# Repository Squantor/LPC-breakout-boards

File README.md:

# LPC microcontroller breakout boards
This is a small collection breakout boards for various LPC microcontrollers, in the future I might add others to the mix. Currently there are a set of eagle and kicad designs, the eagle designs are legacy and might get replaced in the future as currently I am fully comitting on using kicad.
## checkout notes
This repository contains a few submodules, so after checking out do not forget to also check out the submodules.
```
git clone https://github.com/Squantor/LPC-breakout-boards.git
git submodule init
git submodule update
```
Submodules are my private kicad library that are used in my projects. I do try to use the kicad components as much as possible but for certain component types they are less then optimal.

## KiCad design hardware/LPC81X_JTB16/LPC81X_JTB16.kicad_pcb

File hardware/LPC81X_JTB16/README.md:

# LPC812 XSON16 breakout
Breakout board for the LPC812 in XSON16 package. This is more or less a test bed to do everything as small as possible. So 0201 components, tiny crystal, everything tiny!
## TODO's
Still some things need to be done:
* schematic entry 
* PCB layout
* Review with one night in between
* Produce at [OSHPARK](https://oshpark.com/)
* Assemble
* Test & characterise
* update Readme.md with pictures and BOM
## BOM
* LPC812M101JTB16
* All passives are 0201

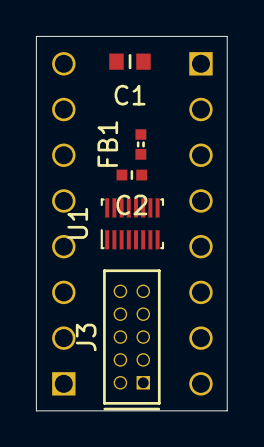
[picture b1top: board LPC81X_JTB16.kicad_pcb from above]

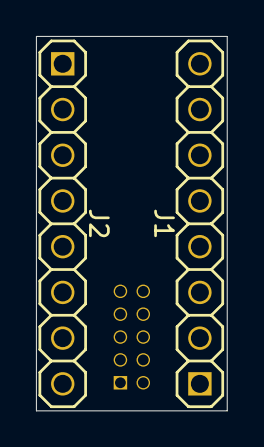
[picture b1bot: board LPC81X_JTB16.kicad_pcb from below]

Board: 2 copper layers, 10.6 x 20.8 mm, 9 parts (2 on the bottom side), 11 nets, no tracks yet.

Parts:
C1: 10u; C_0603
C2: 1u; C_0402
FB1: 600; L_0402
J1, J2: Conn_01x08; Header-0254-1X08-H010
J3: JTAG_2X05_IN; Header-0127-2X05-H006
N1: 20200720; Label_Generic
N2: OHWLOGO; OSHW-Symbol_6.7x6mm_SilkScreen
U1: LPC812M101JTB16; NXP_XSON-16

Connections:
/PIO0_2: J2.7, U1.6
/PIO0_3: J2.8, U1.5
/PIO0_4: J1.1, U1.4
/PIO0_5: J1.2, U1.3
/PIO0_10: J2.5, U1.8
/PIO0_11: J2.6, U1.7
/PIO0_12: J1.3, U1.2
/PIO0_13: J1.4, U1.1
/VDD: C1.1, FB1.2, J3.1
/VSS: C1.2, C2.2, J3.3, J3.5, J3.9, U1.13
unnamed: C2.1, FB1.1, U1.12

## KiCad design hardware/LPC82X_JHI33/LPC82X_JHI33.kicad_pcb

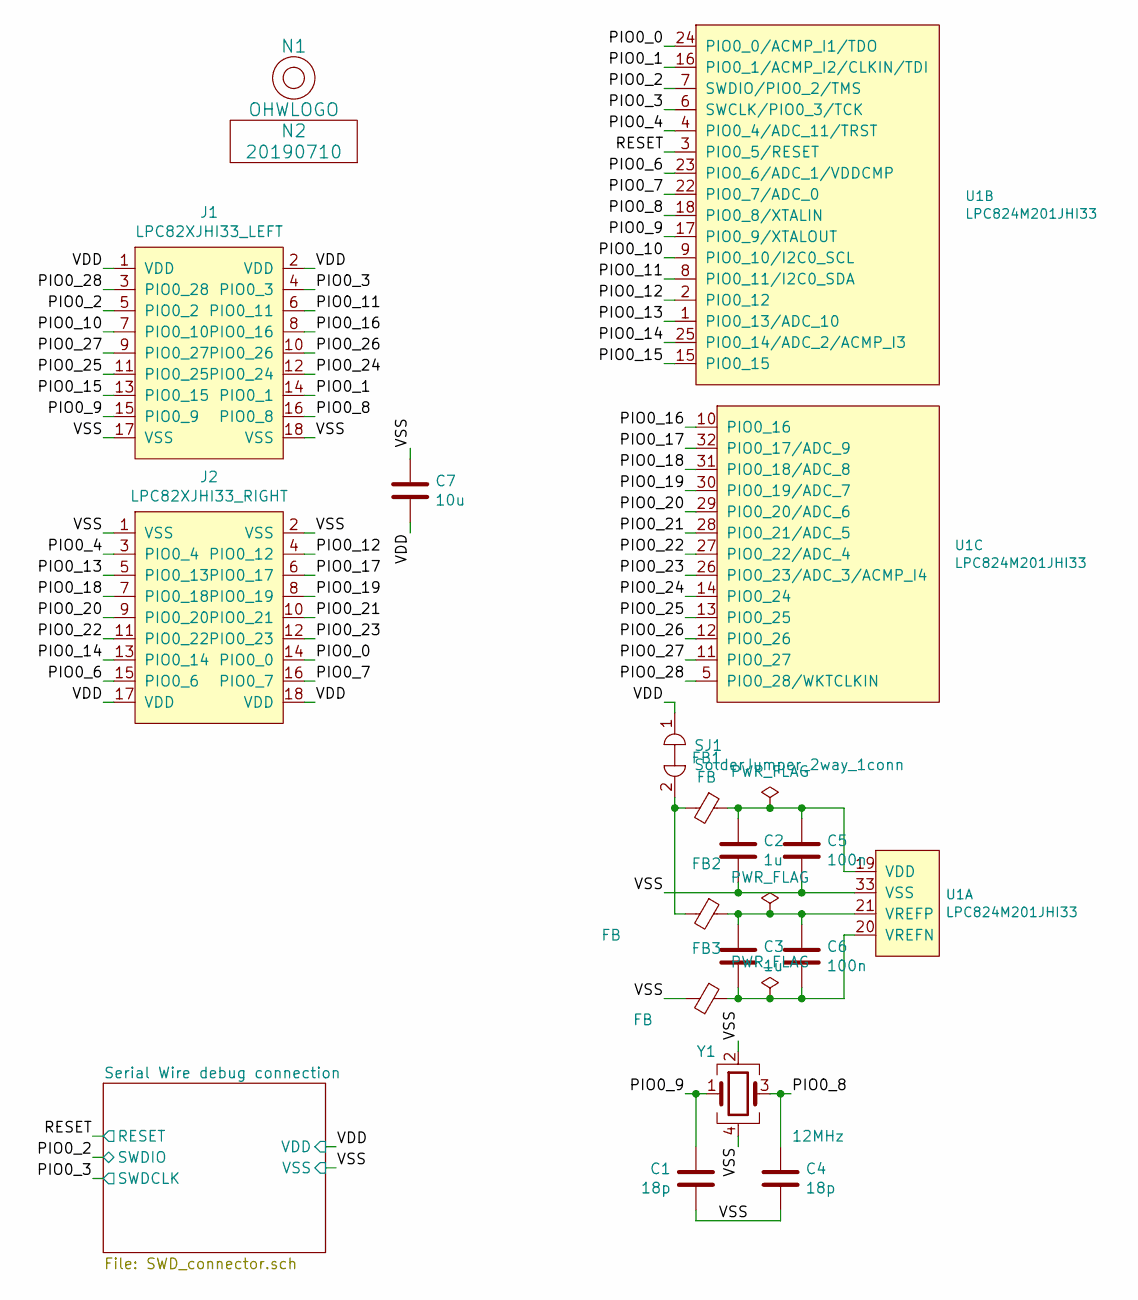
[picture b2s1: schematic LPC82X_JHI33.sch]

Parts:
C1, C4: 18p; C_0402
C2, C3: 1u; C_0603
C5, C6: 100n; C_0402
C7: 10u; C_0805
FB1, FB2, FB3: FB; C_0402
J1: LPC82XJHI33_LEFT; LPC82XJHI33_breakout_left
J2: LPC82XJHI33_RIGHT; LPC82XJHI33_breakout_right
N1: OHWLOGO; OSHW-Symbol_6.7x6mm_SilkScreen
N2: 20190710; Label_version
SJ1: SolderJumper_2way_1conn; solder_jumper_2way_conn
U1: LPC824M201JHI33; SOT617-3_alt_paste
Y1: 12MHz; Crystal_3225_4

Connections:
/PIO0_0: J2.14 (PIO0_0), U1.24 (PIO0_0/ACMP_I1/TDO)
/PIO0_1: J1.14 (PIO0_1), U1.16 (PIO0_1/ACMP_I2/CLKIN/TDI)
/PIO0_2: J1.5 (PIO0_2), U1.7 (SWDIO/PIO0_2/TMS); also elsewhere on the board
/PIO0_3: J1.4 (PIO0_3), U1.6 (SWCLK/PIO0_3/TCK); also elsewhere on the board
/PIO0_4: J2.3 (PIO0_4), U1.4 (PIO0_4/ADC_11/TRST)
/PIO0_6: J2.15 (PIO0_6), U1.23 (PIO0_6/ADC_1/VDDCMP)
/PIO0_7: J2.16 (PIO0_7), U1.22 (PIO0_7/ADC_0)
/PIO0_8: C4.1, J1.16 (PIO0_8), U1.18 (PIO0_8/XTALIN), Y1.3
/PIO0_9: C1.1, J1.15 (PIO0_9), U1.17 (PIO0_9/XTALOUT), Y1.1
/PIO0_10: J1.7 (PIO0_10), U1.9 (PIO0_10/I2C0_SCL)
/PIO0_11: J1.6 (PIO0_11), U1.8 (PIO0_11/I2C0_SDA)
/PIO0_12: J2.4 (PIO0_12), U1.2 (PIO0_12)
/PIO0_13: J2.5 (PIO0_13), U1.1 (PIO0_13/ADC_10)
/PIO0_14: J2.13 (PIO0_14), U1.25 (PIO0_14/ADC_2/ACMP_I3)
/PIO0_15: J1.13 (PIO0_15), U1.15 (PIO0_15)
/PIO0_16: J1.8 (PIO0_16), U1.10 (PIO0_16)
/PIO0_17: J2.6 (PIO0_17), U1.32 (PIO0_17/ADC_9)
/PIO0_18: J2.7 (PIO0_18), U1.31 (PIO0_18/ADC_8)
/PIO0_19: J2.8 (PIO0_19), U1.30 (PIO0_19/ADC_7)
/PIO0_20: J2.9 (PIO0_20), U1.29 (PIO0_20/ADC_6)
/PIO0_21: J2.10 (PIO0_21), U1.28 (PIO0_21/ADC_5)
/PIO0_22: J2.11 (PIO0_22), U1.27 (PIO0_22/ADC_4)
/PIO0_23: J2.12 (PIO0_23), U1.26 (PIO0_23/ADC_3/ACMP_I4)
/PIO0_24: J1.12 (PIO0_24), U1.14 (PIO0_24)
/PIO0_25: J1.11 (PIO0_25), U1.13 (PIO0_25)
/PIO0_26: J1.10 (PIO0_26), U1.12 (PIO0_26)
/PIO0_27: J1.9 (PIO0_27), U1.11 (PIO0_27)
/PIO0_28: J1.3 (PIO0_28), U1.5 (PIO0_28/WKTCLKIN)
/RESET: U1.3 (PIO0_5/RESET); also elsewhere on the board
/VDD: C7.2, J1.1 (VDD), J1.2 (VDD), J2.17 (VDD), J2.18 (VDD), SJ1.1; also elsewhere on the board
/VSS: C1.2, C2.2, C4.2, C5.2, C7.1, FB3.2, J1.17 (VSS), J1.18 (VSS), J2.1 (VSS), J2.2 (VSS), U1.33 (VSS), Y1.2, Y1.4; also elsewhere on the board
unnamed: C2.1, C5.1, FB1.1, U1.19 (VDD)
unnamed: C3.1, C6.1, FB2.1, U1.21 (VREFP)
unnamed: C3.2, C6.2, FB3.1, U1.20 (VREFN)
unnamed: FB1.2, FB2.2, SJ1.2

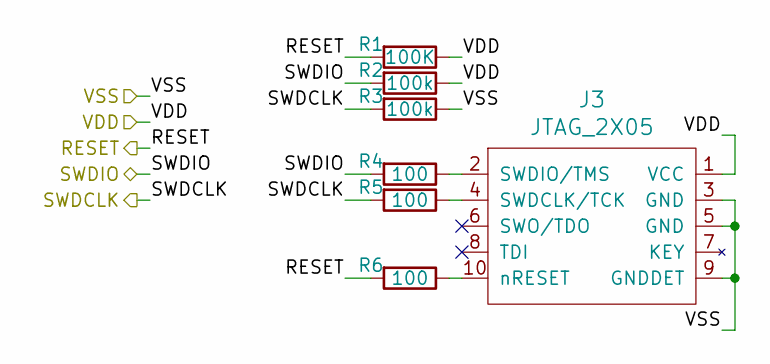
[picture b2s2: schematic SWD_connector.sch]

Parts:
J3: JTAG_2X05; Header-0127-2X05-H006
R1: 100K; R_0402_hand
R2, R3: 100k; R_0402_hand
R4, R5, R6: 100; R_0402_hand

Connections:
/PIO0_2: R2.2, R4.2; also elsewhere on the board
/PIO0_3: R3.2, R5.2; also elsewhere on the board
/RESET: R1.2, R6.2; also elsewhere on the board
/VDD: J3.1 (VCC), R1.1, R2.1; also elsewhere on the board
/VSS: J3.3 (GND), J3.5 (GND), J3.9 (GNDDET), R3.1; also elsewhere on the board
unnamed: J3.2 (SWDIO/TMS), R4.1
unnamed: J3.4 (SWDCLK/TCK), R5.1
unnamed: J3.10 (nRESET), R6.1

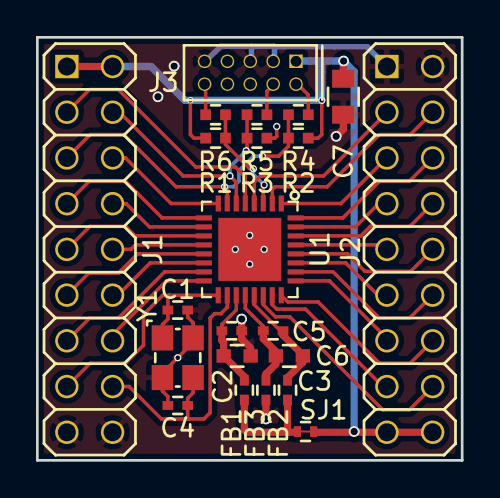
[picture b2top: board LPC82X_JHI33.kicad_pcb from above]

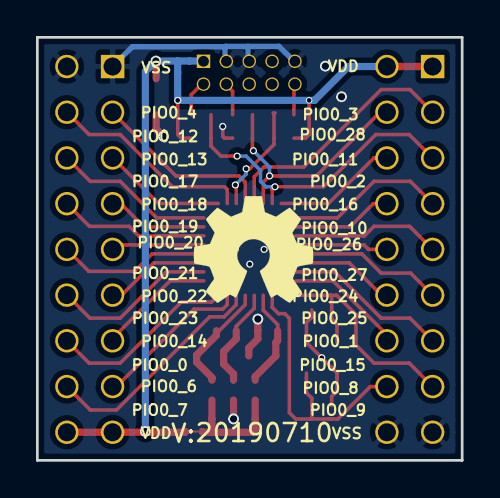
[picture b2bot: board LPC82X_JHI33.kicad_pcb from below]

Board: 2 copper layers, 23.6 x 23.5 mm, 24 parts (2 on the bottom side), 38 nets.

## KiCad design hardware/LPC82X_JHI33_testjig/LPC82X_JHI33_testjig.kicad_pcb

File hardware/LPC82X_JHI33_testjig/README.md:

# LPC824JHI33 test jig PCB
This PCB is used in the LPC824JHI33 test jig. It contains a network of resistors and capacitors that is used by the test algorithm. See in the software directory the breakout tester how this works in detail.
## TODO's
Still some things need to be done:
* schematic entry (TODO)
* PCB layout (TODO)
* Review with one night in between (TODO)
* Produce at [OSHPARK](https://oshpark.com/) (TODO)
* Assemble (TODO)
* Test & characterise (TODO)
* update Readme.md with pictures and BOM (TODO)

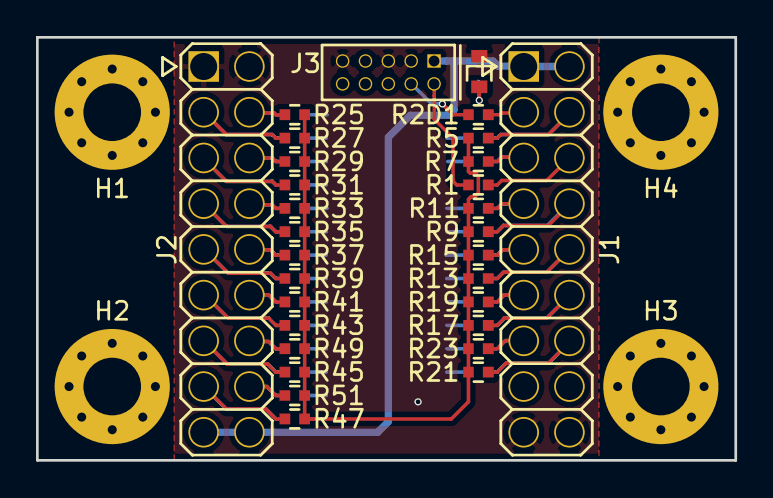
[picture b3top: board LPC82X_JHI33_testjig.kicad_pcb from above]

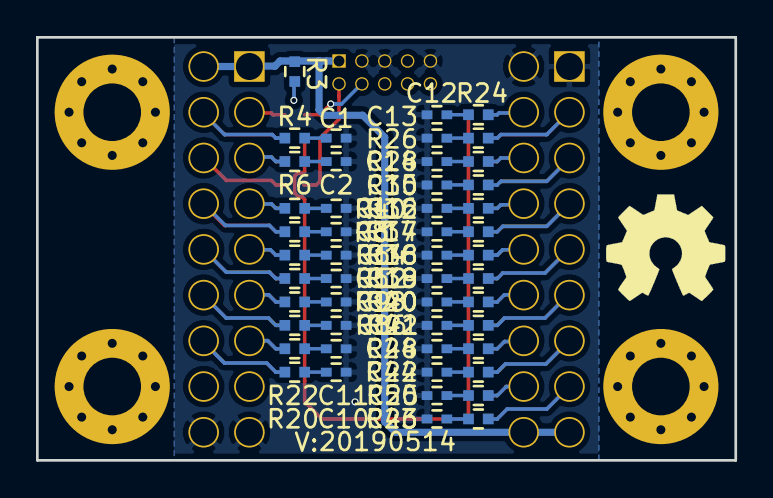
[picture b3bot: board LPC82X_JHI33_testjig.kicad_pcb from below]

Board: 2 copper layers, 38.8 x 23.5 mm, 85 parts (51 on the bottom side), 56 nets.

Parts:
C1, C2, C3, C4, C5, C6, C8, C9, C10, C11, C12, C13, C14, C15, C16, C17, C18, C19, C20, C21, C22, C23, C24, C25: 1u; C_0402
D1: RED; D_0603_hand
H1, H2, H3, H4: MountingHole; MountingHole_3.2mm_M3_Pad_Via
J1: LPC82XJHI33_LEFT; Header-0254-2X09-H015
J2: LPC82XJHI33_RIGHT; Header-0254-2X09-H015
J3: JTAG_2X05; Header-0127-2X05-H006
N1: OHWLOGO; OSHW-Symbol_6.7x6mm_SilkScreen
N2: 20190514; Label_version
R1, R2: 100; R_0402_hand
R3: 1K; R_0402_hand
R4, R6, R8, R10, R12, R14, R16, R18, R20, R22, R24, R26, R28, R30, R32, R34, R36, R38, R40, R42, R44, R46, R48, R50: 470; R_0402_hand
R5, R7, R9, R11, R13, R15, R17, R19, R21, R23, R25, R27, R29, R31, R33, R35, R37, R39, R41, R43, R45, R47, R49, R51: 100K; R_0402_hand

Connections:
/Digital_stimulus: R5.1, R7.1, R9.1, R11.1, R13.1, R15.1, R17.1, R19.1, R21.1, R23.1, R25.1, R27.1, R29.1, R31.1, R33.1, R35.1, R37.1, R39.1, R41.1, R43.1, R45.1, R47.1, R49.1, R51.1
/PIO0_0: J2.13, R44.2, R45.2
/PIO0_1: J1.13, R22.2, R23.2
/PIO0_2: J1.6, R1.2
/PIO0_3: J1.3, R2.2
/PIO0_4: J2.4, R24.2, R25.2
/PIO0_6: J2.16, R50.2, R51.2
/PIO0_7: J2.15, R46.2, R47.2
/PIO0_10: J1.8, R8.2, R9.2
/PIO0_11: J1.5, R6.2, R7.2
/PIO0_12: J2.3, R26.2, R27.2
/PIO0_13: J2.6, R28.2, R29.2
/PIO0_14: J2.14, R48.2, R49.2
/PIO0_15: J1.14, R20.2, R21.2
/PIO0_16: J1.7, R10.2, R11.2
/PIO0_17: J2.5, R30.2, R31.2
/PIO0_18: J2.8, R32.2, R33.2
/PIO0_19: J2.7, R34.2, R35.2
/PIO0_20: J2.10, R36.2, R37.2
/PIO0_21: J2.9, R38.2, R39.2
/PIO0_22: J2.12, R40.2, R41.2
/PIO0_23: J2.11, R42.2, R43.2
/PIO0_24: J1.11, R18.2, R19.2
/PIO0_25: J1.12, R16.2, R17.2
/PIO0_26: J1.9, R14.2, R15.2
/PIO0_27: J1.10, R12.2, R13.2
/PIO0_28: J1.4, R4.2, R5.2
/VDD: J1.1, J1.2, J2.17, J2.18, J3.1, R3.1
/VSS: C1.2, C2.2, C3.2, C4.2, C5.2, C6.2, C8.2, C9.2, C10.2, C11.2, C12.2, C13.2, C14.2, C15.2, C16.2, C17.2, C18.2, C19.2, C20.2, C21.2, C22.2, C23.2, C24.2, C25.2, D1.1, J1.17, J1.18, J2.1, J2.2, J3.3, J3.5, J3.9
unnamed: C1.1, R4.1
unnamed: C2.1, R6.1
unnamed: C3.1, R8.1
unnamed: C4.1, R10.1
unnamed: C5.1, R12.1
unnamed: C6.1, R14.1
unnamed: C8.1, R16.1
unnamed: C9.1, R18.1
unnamed: C10.1, R20.1
unnamed: C11.1, R22.1
unnamed: C12.1, R24.1
unnamed: C13.1, R26.1
unnamed: C14.1, R28.1
unnamed: C15.1, R30.1
unnamed: C16.1, R32.1
unnamed: C17.1, R34.1
unnamed: C18.1, R36.1
unnamed: C19.1, R38.1
unnamed: C20.1, R40.1
unnamed: C21.1, R42.1
unnamed: C22.1, R44.1
unnamed: C23.1, R46.1
unnamed: C24.1, R48.1
unnamed: C25.1, R50.1
unnamed: D1.2, R3.2
unnamed: J3.2, R1.1
unnamed: J3.4, R2.1

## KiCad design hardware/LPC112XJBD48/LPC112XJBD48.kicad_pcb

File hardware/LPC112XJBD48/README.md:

# LPC112X QFP48 breakout board
Breakout board of [LPC112X](https://www.nxp.com/products/processors-and-microcontrollers/arm-based-processors-and-mcus/lpc-cortex-m-mcus/lpc1100-cortex-m0-plus-m0/scalable-entry-level-32-bit-microcontroller-mcu-based-on-arm-cortex-m0-cores:LPC1100)
## TODO's
Still some things need to be done:
* schematic entry (TODO)
* PCB layout (TODO)
* Review with one night in between (TODO)
* Produce at [OSHPARK](https://oshpark.com/) (TODO)
* Assemble (TODO)
* Test & characterise (TODO)
* update Readme.md with pictures and BOM (TODO)

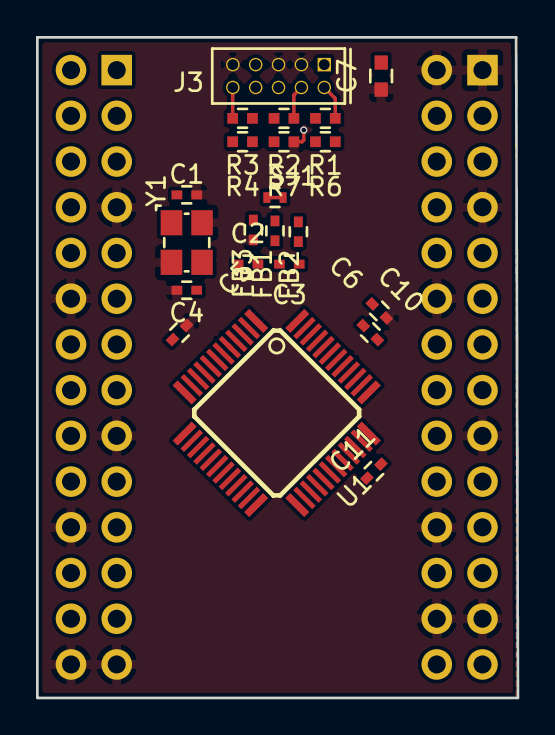
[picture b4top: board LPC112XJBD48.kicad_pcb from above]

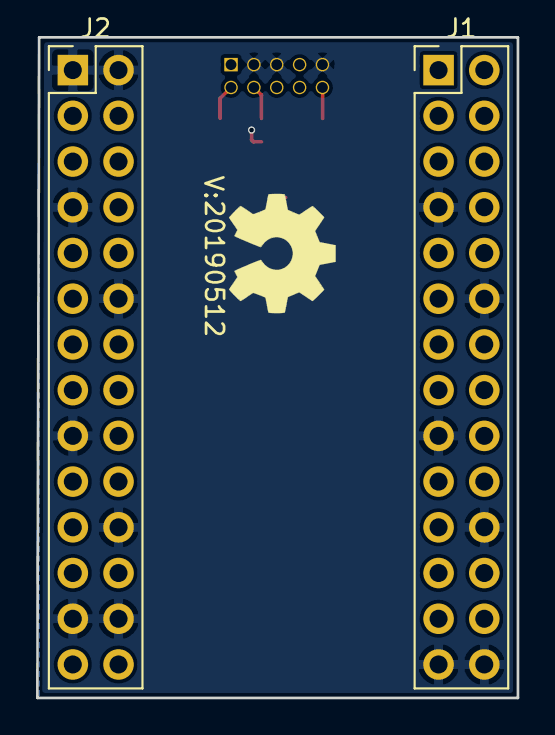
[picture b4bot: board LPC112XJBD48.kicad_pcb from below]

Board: 2 copper layers, 26.7 x 36.7 mm, 26 parts (4 on the bottom side), 49 nets.

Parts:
C1, C4: 18p; C_0402
C2, C3: 1u; C_0402
C5, C6, C10, C11: 100n; C_0402
C7: 10u; C_0603
FB1, FB2, FB3: 600; C_0402
J1, J2: Conn_02x14_Odd_Even; PinHeader_2x14_P2.54mm_Vertical
J3: JTAG_2X05; Header-0127-2X05-H006
N1: OHWLOGO; OSHW-Symbol_6.7x6mm_SilkScreen
N2: 20190512; Label_version
R1, R2, R3: 100; R_0402_hand
R4: 100K; R_0402_hand
R6, R7: 100k; R_0402_hand
SJ1: SolderJumper_2way_1conn; solder_jumper_2way_conn
U1: LPC1125JBD48_303; SOT313-2-NXP
Y1: 12MHz; Crystal_3225_4

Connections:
/PIO0_1: J1.6, U1.4
/PIO0_2: J1.9, U1.10
/PIO0_3: J1.14, U1.14
/PIO0_4: J1.15, U1.15
/PIO0_5: J1.16, U1.16
/PIO0_6: J1.24, U1.22
/PIO0_7: J1.25, U1.23
/PIO0_8: J2.23, U1.26
/PIO0_9: J2.21, U1.27
/PIO0_10: J2.20, R2.2, R7.2, U1.28
/PIO0_11: J2.18, U1.30
/PIO1_0: J2.16, U1.31
/PIO1_1: J2.15, U1.32
/PIO1_2: J2.14, U1.35
/PIO1_3: J2.10, R1.2, R6.2, U1.38
/PIO1_4: J2.9, U1.39
/PIO1_5: J2.6, U1.45
/PIO1_6: J2.5, U1.46
/PIO1_7: J2.4, U1.47
/PIO1_8: J1.8, U1.9
/PIO1_9: J1.18, U1.17
/PIO1_10: J2.19, U1.29
/PIO1_11: J2.8, U1.42
/PIO2_0: J1.4, U1.2
/PIO2_1: J1.13, U1.13
/PIO2_2: J2.24, U1.25
/PIO2_3: J2.11, U1.37
/PIO2_4: J1.20, U1.19
/PIO2_5: J1.21, U1.20
/PIO2_6: J1.3, U1.1
/PIO2_7: J1.10, U1.11
/PIO2_8: J1.11, U1.12
/PIO2_9: J1.26, U1.24
/PIO3_0: J2.13, U1.36
/PIO3_3: J2.3, U1.48
/PIO3_4: J1.19, U1.18
/PIO3_5: J1.23, U1.21
/RESET: J1.5, R3.2, R4.2, U1.3
/XTALIN: C4.1, U1.6, Y1.3
/XTALOUT: C1.1, U1.7, Y1.1
unnamed: C2.1, C5.1, C10.1, FB1.1, U1.8, U1.44
unnamed: C3.1, C6.1, C11.1, FB2.1, U1.33, U1.43
unnamed: C3.2, C6.2, C11.2, FB3.1, U1.34, U1.40
unnamed: FB1.2, FB2.2, SJ1.1
unnamed: J3.2, R1.1
unnamed: J3.4, R2.1
unnamed: J3.10, R3.1
VDD: C7.2, J1.1, J1.2, J2.27, J2.28, J3.1, R4.1, R6.1, SJ1.2
VSS: C1.2, C2.2, C4.2, C5.2, C7.1, C10.2, FB3.2, J1.7, J1.12, J1.17, J1.22, J1.27, J1.28, J2.1, J2.2, J2.7, J2.12, J2.17, J2.22, J2.25, J2.26, J3.3, J3.5, J3.9, R7.1, U1.5, U1.41, Y1.2, Y1.4

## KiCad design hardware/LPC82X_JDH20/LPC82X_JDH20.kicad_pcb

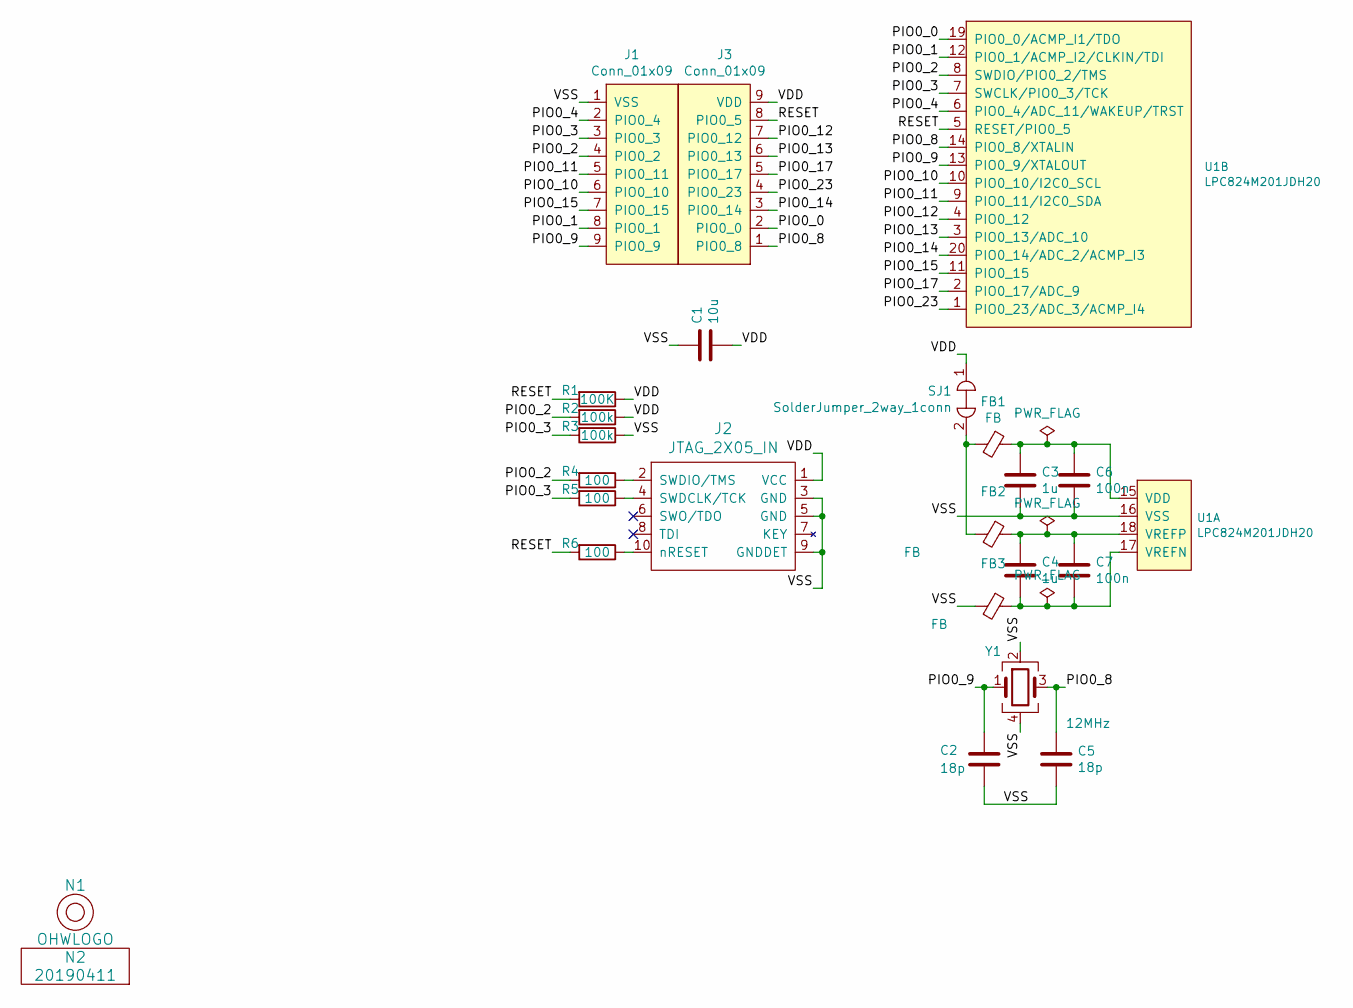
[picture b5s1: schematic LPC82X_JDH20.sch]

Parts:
C1: 10u; C_0805
C2, C5: 18p; C_0402
C3, C4: 1u; C_0603
C6, C7: 100n; C_0402
FB1, FB2, FB3: FB; C_0402
J1: Conn_01x09; LPC82XJDH20_breakout_left
J2: JTAG_2X05_IN; Header-0127-2X05-H006
J3: Conn_01x09; LPC82XJDH20_breakout_right
N1: OHWLOGO; OSHW-Symbol_6.7x6mm_SilkScreen
N2: 20190411; Label_version
R1: 100K; R_0402_hand
R2, R3: 100k; R_0402_hand
R4, R5, R6: 100; R_0402_hand
SJ1: SolderJumper_2way_1conn; solder_jumper_2way_conn
U1: LPC824M201JDH20; SOT360
Y1: 12MHz; Crystal_3225_4

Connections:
/PIO0_0: J3.2 (PIO0_0), U1.19 (PIO0_0/ACMP_I1/TDO)
/PIO0_1: J1.8 (PIO0_1), U1.12 (PIO0_1/ACMP_I2/CLKIN/TDI)
/PIO0_2: J1.4 (PIO0_2), R2.2, R4.2, U1.8 (SWDIO/PIO0_2/TMS)
/PIO0_3: J1.3 (PIO0_3), R3.2, R5.2, U1.7 (SWCLK/PIO0_3/TCK)
/PIO0_4: J1.2 (PIO0_4), U1.6 (PIO0_4/ADC_11/WAKEUP/TRST)
/PIO0_8: C5.1, J3.1 (PIO0_8), U1.14 (PIO0_8/XTALIN), Y1.3
/PIO0_9: C2.1, J1.9 (PIO0_9), U1.13 (PIO0_9/XTALOUT), Y1.1
/PIO0_10: J1.6 (PIO0_10), U1.10 (PIO0_10/I2C0_SCL)
/PIO0_11: J1.5 (PIO0_11), U1.9 (PIO0_11/I2C0_SDA)
/PIO0_12: J3.7 (PIO0_12), U1.4 (PIO0_12)
/PIO0_13: J3.6 (PIO0_13), U1.3 (PIO0_13/ADC_10)
/PIO0_14: J3.3 (PIO0_14), U1.20 (PIO0_14/ADC_2/ACMP_I3)
/PIO0_15: J1.7 (PIO0_15), U1.11 (PIO0_15)
/PIO0_17: J3.5 (PIO0_17), U1.2 (PIO0_17/ADC_9)
/PIO0_23: J3.4 (PIO0_23), U1.1 (PIO0_23/ADC_3/ACMP_I4)
/RESET: J3.8 (PIO0_5), R1.2, R6.2, U1.5 (RESET/PIO0_5)
/VDD: C1.2, J2.1 (VCC), J3.9 (VDD), R1.1, R2.1, SJ1.1
/VSS: C1.1, C2.2, C3.2, C5.2, C6.2, FB3.2, J1.1 (VSS), J2.3 (GND), J2.5 (GND), J2.9 (GNDDET), R3.1, U1.16 (VSS), Y1.2, Y1.4
unnamed: C3.1, C6.1, FB1.1, U1.15 (VDD)
unnamed: C4.1, C7.1, FB2.1, U1.18 (VREFP)
unnamed: C4.2, C7.2, FB3.1, U1.17 (VREFN)
unnamed: FB1.2, FB2.2, SJ1.2
unnamed: J2.2 (SWDIO/TMS), R4.1
unnamed: J2.4 (SWDCLK/TCK), R5.1
unnamed: J2.10 (nRESET), R6.1

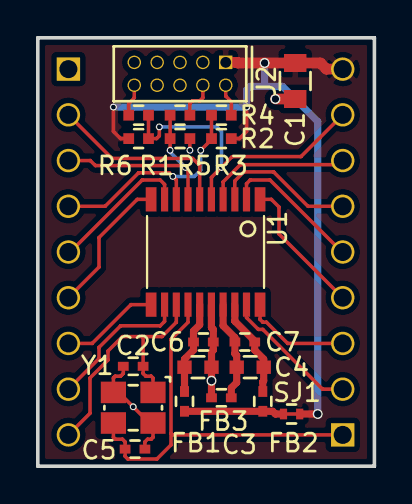
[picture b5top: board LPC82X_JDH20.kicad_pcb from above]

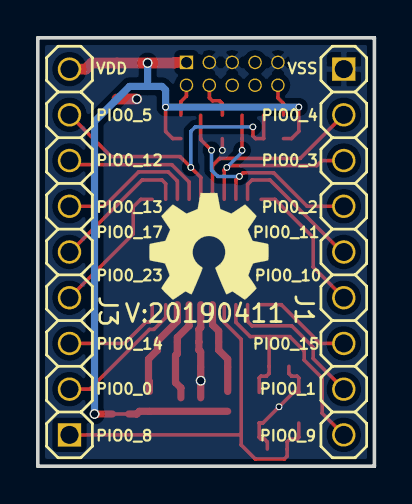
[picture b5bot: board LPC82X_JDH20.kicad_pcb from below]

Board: 2 copper layers, 18.7 x 23.8 mm, 24 parts (4 on the bottom side), 25 nets.

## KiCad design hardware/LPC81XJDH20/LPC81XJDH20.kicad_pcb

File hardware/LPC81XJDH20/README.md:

# LPC81X SSOP20 breakout board
Breakout board of [LPC81X](https://www.nxp.com/products/processors-and-microcontrollers/arm-based-processors-and-mcus/lpc-cortex-m-mcus/lpc800-series-cortex-m0-plus-mcus/low-cost-microcontrollers-mcus-based-on-arm-cortex-m0-plus-cores:LPC81X_LPC83X) microcontroller.
## TODO's
Still some things need to be done:
* Produce at [OSHPARK](https://oshpark.com/shared_projects/42cLyk7C)
* Assemble (TODO)
* Update test program (TODO)
* Update Readme.md with pictures and BOM (TODO)
* Put on sale on tindie

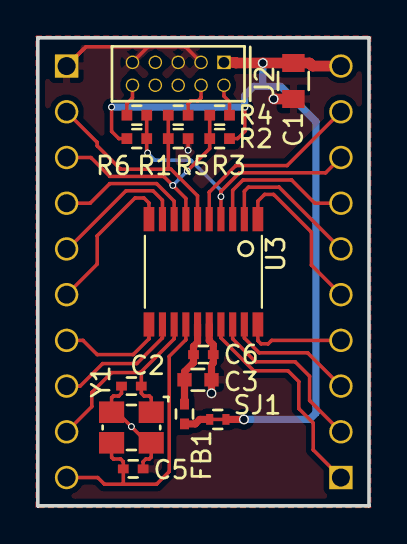
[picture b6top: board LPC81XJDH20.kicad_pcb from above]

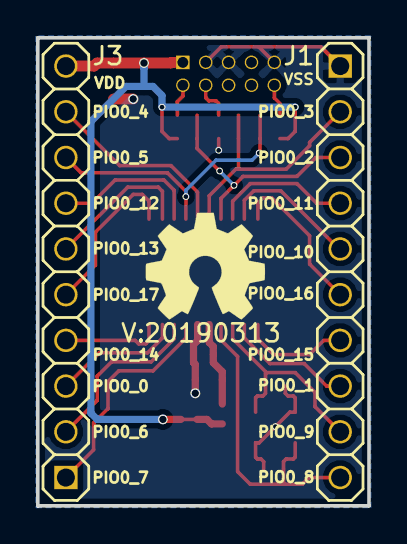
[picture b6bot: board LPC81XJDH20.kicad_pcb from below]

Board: 2 copper layers, 18.4 x 26.0 mm, 20 parts (4 on the bottom side), 25 nets.

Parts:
C1: 10u; C_0805
C2, C5: 18p; C_0402
C3: 1u; C_0603
C6: 100n; C_0402
FB1: FB; C_0402
J1: LPC81XJDH20_breakout_left
J2: JTAG_2X05; Header-0127-2X05-H006
J3: LPC81XJDH20_breakout_right
N1: OHWLOGO; OSHW-Symbol_6.7x6mm_SilkScreen
N2: 20190313; Label_version
R1: 100K; R_0402_hand
R2, R3: 100k; R_0402_hand
R4, R5, R6: 33; R_0402_hand
SJ1: SolderJumper_2way_1conn; solder_jumper_2way_conn
U3: LPC812M101JDH20; SOT360
Y1: 12MHz; Crystal_3225_4

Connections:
/PIO0_0: J3.3, U3.19
/PIO0_1: J1.8, U3.12
/PIO0_2: J1.3, R2.2, R4.2, U3.7
/PIO0_3: J1.2, R3.2, R5.2, U3.6
/PIO0_4: J3.9, U3.5
/PIO0_6: J3.2, U3.18
/PIO0_7: J3.1, U3.17
/PIO0_8: C5.1, J1.10, U3.14, Y1.3
/PIO0_9: C2.1, J1.9, U3.13, Y1.1
/PIO0_10: J1.5, U3.9
/PIO0_11: J1.4, U3.8
/PIO0_12: J3.7, U3.3
/PIO0_13: J3.6, U3.2
/PIO0_14: J3.4, U3.20
/PIO0_15: J1.7, U3.11
/PIO0_16: J1.6, U3.10
/PIO0_17: J3.5, U3.1
/RESET: J3.8, R1.2, R6.2, U3.4
unnamed: C3.1, C6.1, FB1.1, U3.15
unnamed: FB1.2, SJ1.2
unnamed: J2.2, R4.1
unnamed: J2.4, R5.1
unnamed: J2.10, R6.1
VDD: C1.2, J2.1, J3.10, R1.1, R2.1, SJ1.1
VSS: C1.1, C2.2, C3.2, C5.2, C6.2, J1.1, J2.3, J2.5, J2.9, R3.1, U3.16, Y1.2, Y1.4

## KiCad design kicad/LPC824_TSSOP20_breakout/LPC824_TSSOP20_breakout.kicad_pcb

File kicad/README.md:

# KiCad LPC breakout boards
We have here a bunch of LPC series microcontroller breakouts. Each of the kicad project dirs contains its own README.
All of the breakouts are using the [squantorPcbLibrary](https://github.com/Squantor/squantorPcbLibrary.git) where needed. Gerbers, and other plots are located per project but only when they have been sent off to production.

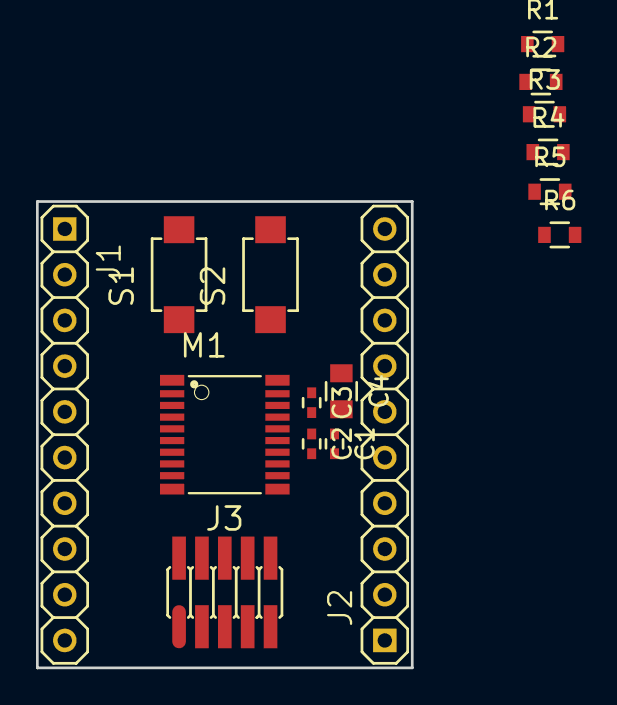
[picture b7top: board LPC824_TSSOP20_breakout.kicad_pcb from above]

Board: 2 copper layers, 20.8 x 25.9 mm, 16 parts (0 on the bottom side), 20 nets, no tracks yet.

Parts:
C1, C3: 100n; C_0402
C2: 10n; C_0402
C4: 10u; C_0805
J1, J2: PINS_1X10; SquantorConnectors-1X10_SMALL
J3: JTAG_2X05; Header-0127-2X05-SMD
M1: LPC824M201JDH20; SOT360
R1, R2: 0; R_0603_hand
R3: 100k; R_0603_hand
R4: 10k; R_0603_hand
R5, R6: 10K; R_0603_hand
S1, S2: 2pin_tact_switch; TD-85XU

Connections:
/AGND: C3.2, C4.2, J2.7, M1.17, R2.1
/AVCC: C3.1, C4.1, J2.8, M1.18, R1.1
/GND: C1.2, C2.2, J2.5, J3.3, J3.5, J3.9, M1.15, R2.2, R6.1, S1.2, S2.2
/PIO0_0: J2.9, M1.19
/PIO0_1: J2.2, M1.12
/PIO0_2: J1.8, J3.2, M1.8, R5.2
/PIO0_3: J1.7, J3.4, M1.7, R6.2
/PIO0_4: J1.6, M1.6
/PIO0_5: J1.5, J3.10, M1.5, R3.2, S1.1
/PIO0_8: J2.4, M1.14
/PIO0_9: J2.3, M1.13
/PIO0_10: J1.10, M1.10
/PIO0_11: J1.9, M1.9
/PIO0_12: J1.4, M1.4, R4.2, S2.1
/PIO0_13: J1.3, M1.3
/PIO0_14: J2.10, M1.20
/PIO0_15: J2.1, M1.11
/PIO0_17: J1.2, M1.2
/PIO0_23: J1.1, M1.1
/VCC: C1.1, C2.1, J2.6, J3.1, M1.16, R1.2, R3.1, R4.1, R5.1

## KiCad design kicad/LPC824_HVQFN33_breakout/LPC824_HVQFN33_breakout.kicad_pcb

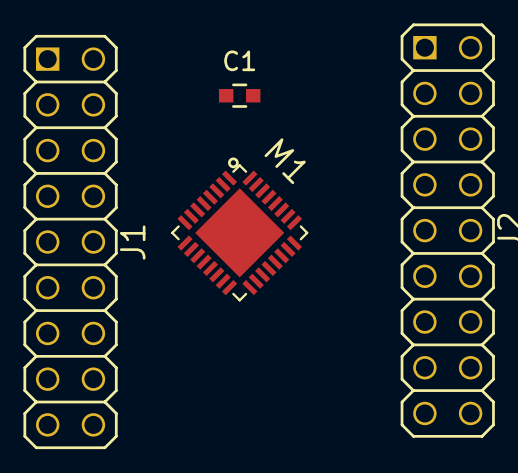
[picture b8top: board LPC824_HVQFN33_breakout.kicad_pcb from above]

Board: 2 copper layers, 4 parts (0 on the bottom side), 26 nets, no tracks yet.

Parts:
C1: C; C_0603
J1, J2: PINS_2X09; Header-0254-2X09-H010
M1: LPC824M201JHI33; SOT617-3

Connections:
/AGND: J2.15, M1.20
/AREF: J2.14, M1.21
/GND: C1.2, J1.17, J1.18, M1.33
/PIO0_1: J1.15, M1.16
/PIO0_2: J1.8, M1.7
/PIO0_3: J1.5, M1.6
/PIO0_4: J1.3, M1.4
/PIO0_5: J1.4, M1.3
/PIO0_8: J2.17, M1.18
/PIO0_9: J2.18, M1.17
/PIO0_10: J1.10, M1.9
/PIO0_11: J1.7, M1.8
/PIO0_12: J1.1, M1.2
/PIO0_13: J1.2, M1.1
/PIO0_15: J1.16, M1.15
/PIO0_16: J1.9, M1.10
/PIO0_17: J2.1, M1.32
/PIO0_18: J2.2, M1.31
/PIO0_19: J2.3, M1.30
/PIO0_20: J2.4, M1.29
/PIO0_24: J1.13, M1.14
/PIO0_25: J1.14, M1.13
/PIO0_26: J1.11, M1.12
/PIO0_27: J1.12, M1.11
/PIO0_28: J1.6, M1.5
/VCC: C1.1, J2.16, M1.19

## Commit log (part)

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2014-04-18 Update README.md
    * Added more clear description and TODO list
2014-04-18 * populating with BRD and SCH files
2014-04-18 * added eagle project file
2014-04-18 * small updates
2014-04-18 * small mods
2014-04-23 Update README.md
    * Improve layout
    * added more TODO's
    * added link to OSHpark and credit inspirational page
    * added status updates
2014-04-24 * small fixes on TODO list
2014-04-24 * updated todo
2014-04-25 * doing some TODO's
2014-04-30 * updated board and schem with todo's
2014-04-30 * updated readme
2014-05-01 * small beautification mods
2014-05-11 * minor updates with silk, pinout documentation, hole expansion
2014-05-13 Update README.md
    Updated status header
2014-05-16 Update README.md
    updated pricing and TODO's
2014-05-29 * small modifications * improved regulator decoupling capacitor position to leave more space for the pinheaders * improved crystal positioning to leave more space for the pinheaders
2014-06-08 * added some pictures and updated the readme
2014-06-23 * Added image exports of schematics and PCB layers
2014-06-24 Update README.md
    Small mod
2014-06-24 Update README.md
    * Added more to do actions
2014-08-11 Update README.md
    * added a few TODO's
2014-09-26 * added low cost lpc812 breadboard breakout (mini)
2014-09-28 * finished LPC800 mini board * fixed pin 1 for JTAG connection - TODO: Printout inspection and checks for the button layout
2014-10-08 * updated boards with cheaper buttons, better layout and indexed JTAG header
2014-10-09 * small changes preparing for commit to OSH park
2014-10-09 * added final bits and pieces * updated readme
2015-02-20 * renamed LPC800 references to LPC81X * started with LPC82X boards, still need to add the MLF style packages
2015-02-26 * started with lpc824 TSSOP breakout
2015-11-22 * fixed some small mistakes
2015-11-22 * project file updates
2017-01-07 * big cleanup/move of files
2017-01-07 * added gitignore file
2017-01-07 * added kicad starts for the LPC824 breakouts
2017-01-09 * added some file ignore wildcards for kicad
2017-01-09 * small updates to the LPC824 breakouts
2017-01-12 * modified eagle project to 7.4
2017-01-12 * updated LPC824 breakout
2017-01-12 * small schematic updates
2017-01-23 * fully connected up connectors - next JTAG connection
2017-01-23 * further layout of the LPC824 chip
2017-03-21 * added a few parts to the LPC824 breakout
2017-03-21 * completed breakout board schematic * started with layout of breakout
2017-03-25 * updated documentation
2017-03-25 * added root readme
2017-03-25 * added documentation
2018-10-26 time to update this project and revisit most of the boards with new insights
2018-10-26 Update README.md
    Whoops, backticks needed for codeblocks
2018-10-26 Update README.md
    Fixing another problem
2018-10-26 regenerated kicad projects with submodule
2018-10-26 started on LPC824 QFN33 breakout
2018-10-26 started with schematic entry of QFN33 LPC824 breakout
2018-10-26 more schematic updates updated footprint of a used button
2018-10-26 updated with solder jumper schematic symbols added some jumpers to the QFN33 breakout
2018-10-26 finished schematic updated new footprints from submodule
2018-10-26 further pcb placement
2018-10-27 started with first layout
2018-10-27 finished routing tracks
2018-10-28 added LPC824 QFN33 breakout on two layers (quicker production) added readme
2018-10-28 differentiating rename from 4 layer to 2 layer
2018-10-28 rename action to explicitly mention layercount
2018-10-28 added bulk decoupling 0805 increased clearance of ground plane
2018-10-28 silk screen updates
2018-10-28 updated versionnumber
2018-10-28 added schematic
2018-10-29 removed absolute path
2018-10-29 removed some parts from schematics to simplify the breakout
2018-10-29 updated schematic bits updated board and rerouted with some deletions, lets see if we can shrink the board a bit
2018-10-30 reduced PCB size, rerouting large parts of it
2018-10-31 updated with new library with jumpers
2018-10-31 updated schematic, added VDD jumper, added top groundplane, completed layout
2018-10-31 updated pcb and fixed some inconsistencies
2018-11-02 some minor trace moves
2018-11-02 updated version number
2018-11-02 added schematic and PCB plots
2018-11-02 pcb update
2018-11-04 copied over schematic, updated libraries
2018-11-04 schematic updates
2018-11-04 updated library references
2018-11-06 updated newer version of PCB library
2018-11-06 updated new libraries
2018-11-06 completed schematic
2018-11-06 updated readme documentation
2018-11-06 started initial PCB layout
2018-11-09 initial component placement
2018-11-09 component placement done
2018-11-09 intermediate layout checkin
2018-11-09 layout done, positioning silk labels
2018-11-09 updated pcb lib
2018-11-09 updated LPC824 component
2018-11-09 updated to new component
2018-11-09 silk placement done
2018-11-09 added schematic plot and PCB gerbers
2018-11-09 adding zips to ignore
2018-11-09 updated a few traces and silk screen bits
2018-11-09 updated PCB library
2018-11-09 updated PCB and plots
2018-11-10 small silk updates, updated values, top groundplane
2018-11-10 updated all plots
2018-11-10 updated readme with newer project
2018-11-21 added paste layers and regenerated gerbers
2018-11-21 updated gerbers, updated generation preferences
2018-11-22 fixed incorrect crystal footprint
2018-11-22 changed via annular rings to 200microns
2018-11-22 updated plots for production
2018-11-22 updated silk mistakes
2018-11-23 updated status
2018-11-23 fixed DRC error on PCB, fixed resistor positions, updated versionnumber
2018-11-23 updated LPC824 QFN33 gerber and schematic plot
2018-11-24 updated versionnumber, fixed unrouted trace
2018-11-24 updated plots
2018-11-25 linked to shared project on OSHpark
2019-01-18 fixed incorrect crystal footprint and relayout
2019-01-18 added some project photos
2019-01-19 newer lpc library
2019-01-19 small trace change, updated version number
2019-01-20 fixed mistake in microcontroller power, updated library component, added newer component library, rerouted
2019-01-21 updated silkscreen
2019-01-21 run DRC
2019-02-15 added first automated board test project
2019-02-15 added LPCopen library for the lpc824
2019-02-15 added lpcopen library to makefile
2019-02-15 added all the needed stuff for blinky
2019-02-15 blinky implemented
2019-02-15 WIP pin test algorithm, added udiv routine
2019-02-15 first testing GPIO works, now to fix all the TODO's
2019-02-15 added explanation for the maximum transition time derivations
2019-02-15 added some delays, need to fix this more nicely
2019-02-15 changed to proper gpio iocon pair type for testing
2019-02-15 added additional check so we never get stuck forever waiting
2019-02-15 added readme explaing what software exists for the breakouts
2019-02-15 newer lpcxpresso library
2019-02-15 updated readme on the LPC82X TSOP20 breakout
2019-02-15 removing old defunct project
2019-02-15 fixed typo in image link
2019-02-15 fixed mistakes in Readme
2019-03-09 reorganising repo
2019-03-09 added LPC112X and LPC81X breakouts
2019-03-10 rename action for LPC82X QFN33 breakout
2019-03-10 more renames
2019-03-10 more renames!
2019-03-10 copied over LPC824 to LPC812
2019-03-10 update submodule
2019-03-10 updated pcb library, replaced LPC824 with LPC812
2019-03-10 added named connector for breakout
2019-03-10 WIP PCB layout
2019-03-10 layout completed
2019-03-10 silk layout completed
2019-03-10 various beauty changes
2019-03-10 copied LPC824 breakout to LPC1125
2019-03-10 schematic entry in progress, added LPC1125
2019-03-11 final small changes to PCB
2019-03-11 fixed mistake with shrunk groundplane, updated readme
2019-03-13 newer LPC812 schematic component, changed paste vs pad
2019-03-13 LPC824 QFN33 new footprint for LPC and shrunk paste size
2019-03-29 updated open drain reason
2019-03-29 updated test software with newer template
2019-03-29 removed defunct files, updated codelite project
2019-03-29 fixing problem with lto
2019-03-31 moving to general purpose breakout tester
2019-03-31 added boards to build system
2019-03-31 moving stuff to board support
2019-03-31 added usb bmp debugging, enable power to jig
2019-03-31 added target power enable/disable commands and scripts
2019-03-31 updated debugging commands, changing build system
2019-03-31 changed breakout name as we have TSSOP20 and QFN33 breakouts
2019-03-31 split up functionality of pin tester
2019-03-31 updated Makefiles
2019-03-31 updated to newer lpc chip
2019-03-31 updated makefiles to support multiple boards
2019-03-31 added LPC81X_JDH20 breakout tests
2019-03-31 fixed problem with lack of division routines in ROM, updated clocking
2019-03-31 gpio tests operational, but still too low timings from Lo to Hi, disabled optimization in Debug
2019-04-04 fixed typo
2019-04-04 fixed bug, reworking pin test algorithm fixed a bug with incorrect MCU selection, pin test algorithm depends too much on gpio characteristics and we dont check both charging slopes
2019-04-04 added TODO for the algorithm, time for sleep
2019-04-09 refactoring and redoing the gpio test routine
2019-04-09 WIP gpio tester
2019-04-09 WIP: completed gpio tester, now testing
2019-04-09 simplified datastructure, increased charge timing
2019-04-09 fine tuned timings
2019-04-10 test routine returns failing GPIO, enabled all pins for LPC812
2019-04-10 fixing failing release build
2019-04-10 cleanup
2019-04-10 updated release debugger settings
2019-04-10 testing LPC82X breakout
2019-04-10 newer PCB library
2019-04-10 added named connectors for LPC82XJDH20 breakout
2019-04-10 ignoring fp-info-cache
2019-04-11 updated silk labels
2019-04-11 changed net names, added named connectors
2019-04-11 pcb net updates
2019-04-11 changed connectors, newer component library
2019-04-12 silk placement completed
2019-04-16 added LPC824 QFN33 ADC evaluator
2019-04-16 updated schematic, partial layout of new planes and reduction of components
2019-04-17 updated to named pcb connectors, further plane addition, inital silk placement
2019-04-24 added embedded library dependency
2019-04-24 added LPC824 tryout, needs cleanup
2019-04-26 newer libEmbeddedC
2019-04-26 tab conversion
2019-04-26 cleanup of project
2019-04-26 more cleanup
2019-04-26 fixed uart output, some cleanup from playground
2019-04-28 changing multi channel sampling
2019-04-28 multi channel sampling, cleanup
2019-04-28 added command prompt to ADC evaluator
2019-05-10 updated libc
2019-05-11 added LPC824 QFN33 testjig PCB project
2019-05-11 routing completed
2019-05-12 schematic addition
2019-05-12 added RED led indicator
2019-05-12 further schematic additions
2019-05-12 further placement of components
2019-05-14 changed silk openings
2019-05-14 silkscreen updates
2019-05-14 updates to paste aperatures, update versionnumber
2019-05-14 fixed weird trace position
2019-05-15 fixed DRC error by updating footprint, rendered plots
2019-05-17 updated libembeddedC
2019-05-21 fixed problem with ADC offset
2019-05-23 reduced sampling rate to improve ADC accuracy
2019-06-18 initial board target for lpc82xJHI33 breakout
2019-06-18 enabled board, defined pins to test
2019-06-18 set board to default to QFN33 board
2019-06-18 reduced lower bound of GPIO test QFN33 test board has 1uF capacitors instead of 2.2uF like the rest, need to update those test jigs
2019-06-18 library updates
2019-06-19 timings to be test jig specific Some jigs have different resistors/capacities
2019-06-19 fine tuned max and min for high low and low high transitions for LPC824JH33 breakouts
2019-06-19 fixed bug that you would never fail on maximum timeouts
2019-06-19 finetuned values for high low and low high maximum and minimum timings
2019-07-10 updated to newer command library
2019-07-10 moved SWD connector to a subschematic
2019-07-10 needed relayout as moving stuff off sheet will reset it
2019-07-10 started with submodules
2019-07-10 updated submodule to include SWD subschematic
2019-07-17 updated to newer LPC824 schematic component
2019-07-19 fixed incorrect path for schematic library
2019-07-19 removing defunc library
2020-07-20 started on LPC812 XSON16 breakout
2020-07-20 updated gitignore with newer files
2020-07-20 WIP schematic definition and raw component placement
